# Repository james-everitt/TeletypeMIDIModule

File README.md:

# TeletypeMIDIModule
I2C to Midi and Eurorack Select Bus

Code adapted from the BPC Txo module
Hardware adapted from the Teletype backpack

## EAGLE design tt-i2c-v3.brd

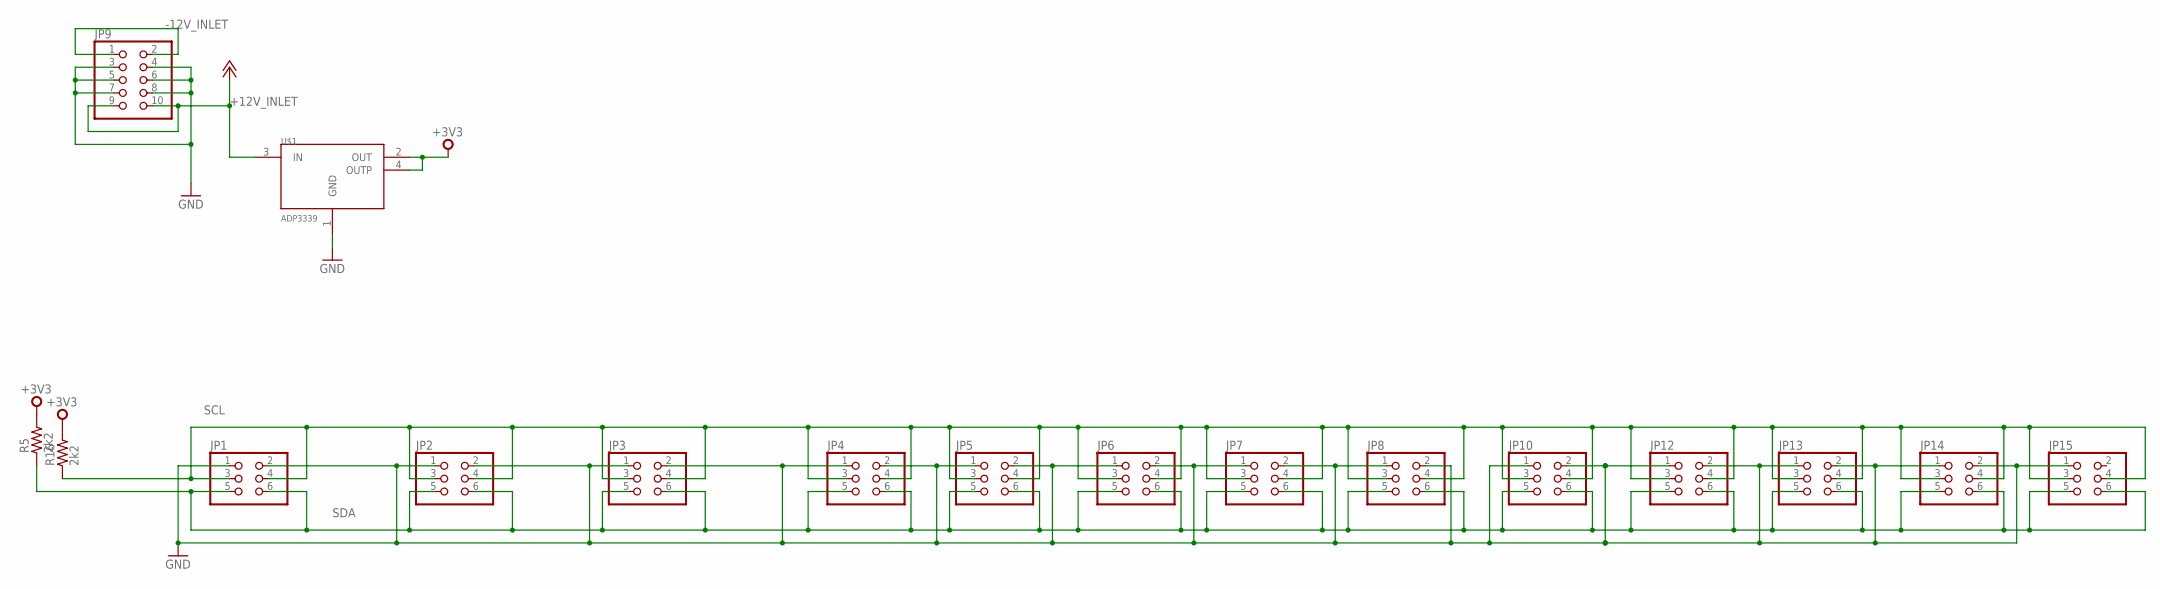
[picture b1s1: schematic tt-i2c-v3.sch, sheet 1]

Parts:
JP1, JP2, JP3, JP4, JP5, JP6, JP7, JP8, JP10, JP12, JP13, JP14, JP15: PINHD-2X3; 2X03
JP9: PINHD-2X5; 2X05
R5, R16: 2k2; R1206
U$1: ADP3339; SOT223

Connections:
+3V3: R5.2, R16.2, U$1.2 (OUT), U$1.4 (OUTP); also elsewhere on the board
+12V_INLET: JP9.9, JP9.10, U$1.3 (IN); also elsewhere on the board
-12V_INLET: JP9.1, JP9.2; also elsewhere on the board
GND: JP1.1, JP1.2, JP2.1, JP2.2, JP3.1, JP3.2, JP4.1, JP4.2, JP5.1, JP5.2, JP6.1, JP6.2, JP7.1, JP7.2, JP8.1, JP8.2, JP9.3, JP9.4, JP9.5, JP9.6, JP9.7, JP9.8, JP10.1, JP10.2, JP12.1, JP12.2, JP13.1, JP13.2, JP14.1, JP14.2, JP15.1, U$1.1 (GND); also elsewhere on the board
SCL: JP1.3, JP1.4, JP2.3, JP2.4, JP3.3, JP3.4, JP4.3, JP4.4, JP5.3, JP5.4, JP6.3, JP6.4, JP7.3, JP7.4, JP8.3, JP8.4, JP10.3, JP10.4, JP12.3, JP12.4, JP13.3, JP13.4, JP14.3, JP14.4, JP15.3, JP15.4, R16.1; also elsewhere on the board
SDA: JP1.5, JP1.6, JP2.5, JP2.6, JP3.5, JP3.6, JP4.5, JP4.6, JP5.5, JP5.6, JP6.5, JP6.6, JP7.5, JP7.6, JP8.5, JP8.6, JP10.5, JP10.6, JP12.5, JP12.6, JP13.5, JP13.6, JP14.5, JP14.6, JP15.5, JP15.6, R5.1; also elsewhere on the board

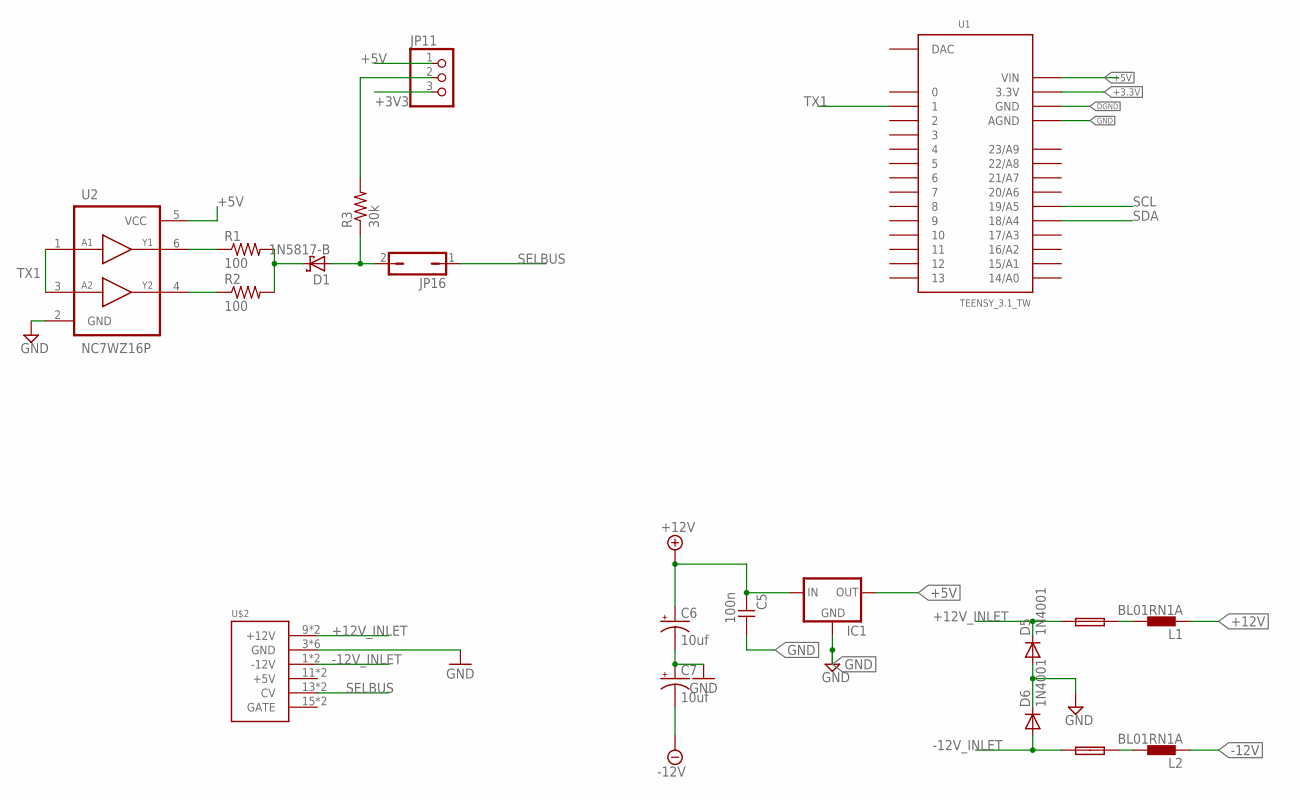
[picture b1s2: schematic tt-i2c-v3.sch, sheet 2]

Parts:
C5: 100n; C050-024X044
C6, C7: 10uf; CPOL-RADIAL-10UF-25V
D1: 1N5817-B; DO41-7.6
D5, D6: 1N4001; DO41-10
F1, F2: FUSE; C050H075X075
IC1: 78LXX
JP11: PINHD-1X3; 1X03
JP16: JP1Q; JP1
L1, L2: BL01RN1A
R1, R2: 100; 0207/7
R3: 30k; 0207/7
U1: TEENSY_3.1_TW
U2: NC7WZ16P; SC70-6
U$2: POWER; POWER_16

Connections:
+3.3V: U1.3.3V
+3V3: JP11.3; also elsewhere on the board
+5V: IC1.OUT, JP11.1, U1.VIN, U2.5 (VCC)
+12V: C5.2, C6.1 (+), IC1.IN, L1.1
+12V_INLET: D5.C, F1.1, U$2.9 (+12V), U$2.10 (+12V); also elsewhere on the board
-12V: C7.2 (-), L2.1
-12V_INLET: D6.A, F2.1, U$2.1 (-12V), U$2.2 (-12V); also elsewhere on the board
DGND: U1.GND
GND: C5.1, C6.2 (-), C7.1 (+), D5.A, D6.C, IC1.GND, U1.AGND, U2.2 (GND), U$2.3 (GND), U$2.4 (GND), U$2.5 (GND), U$2.6 (GND), U$2.7 (GND), U$2.8 (GND); also elsewhere on the board
unnamed: R1.1, U2.6 (Y1)
unnamed: R2.1, U2.4 (Y2)
unnamed: D1.C, R1.2, R2.2
unnamed: JP11.2, R3.2
unnamed: D1.A, JP16.2, R3.1
unnamed: F1.2, L1.2
unnamed: F2.2, L2.2
SCL: U1.19/A5; also elsewhere on the board
SDA: U1.18/A4; also elsewhere on the board
SELBUS: JP16.1, U$2.13 (CV), U$2.14 (CV)
TX1: U1.1, U2.1 (A1), U2.3 (A2)

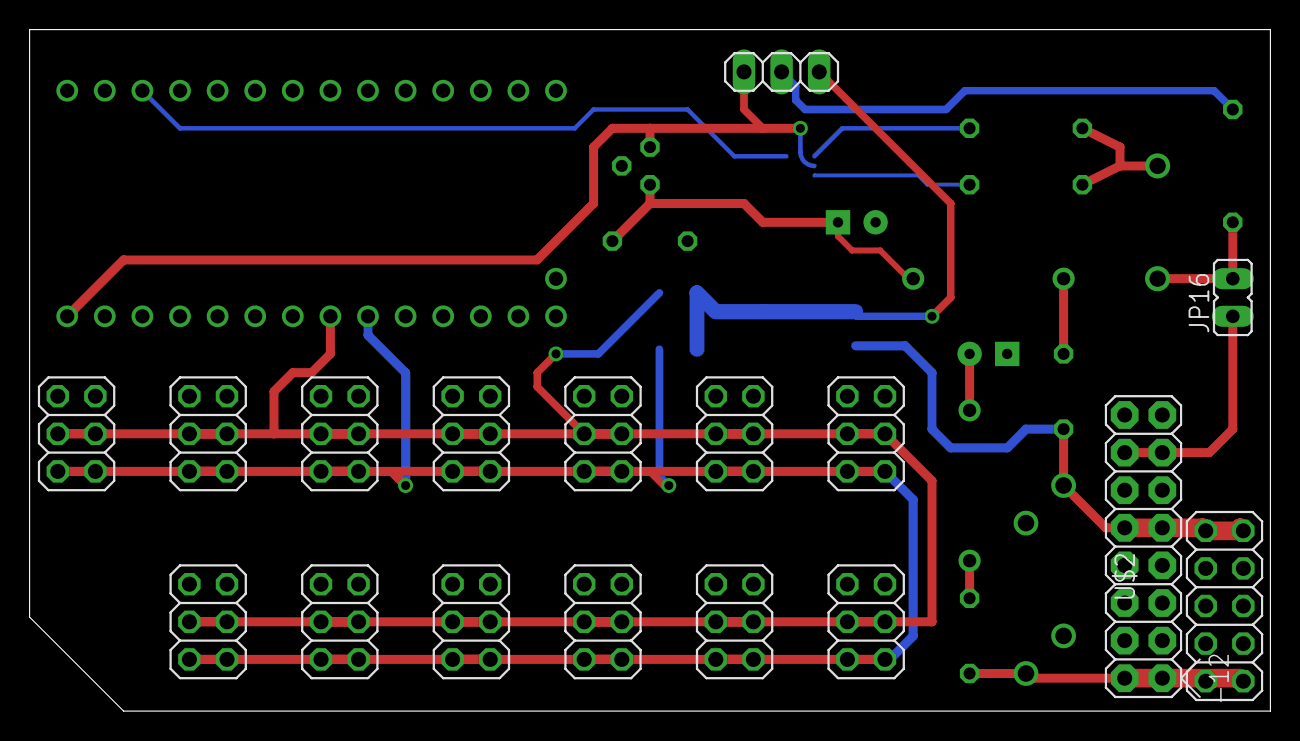
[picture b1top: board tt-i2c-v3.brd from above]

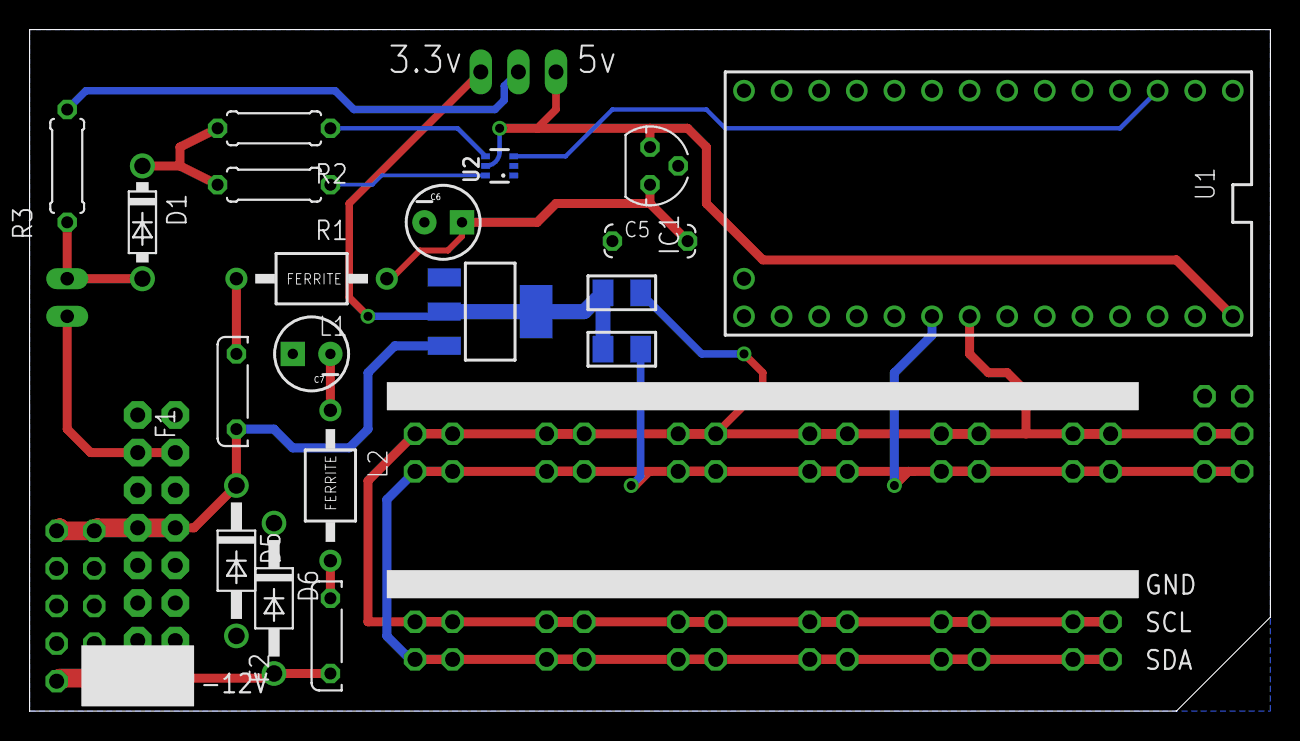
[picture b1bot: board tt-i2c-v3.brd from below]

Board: 2 copper layers, 83.8 x 46.0 mm, 36 parts (19 on the bottom side), 18 nets.

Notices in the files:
parts and their libraries:
SparkFun-Passives: Licensing: CC v3.0 Share-Alike You are welcome to use this library for commercial purposes.
fairchild-semi: Copyright (C) 2010, Bob Starr
